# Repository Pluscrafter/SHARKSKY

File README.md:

# SHARKSKY
Ein Quadrocopter Flightcontroller für eine Maturaarbeit.

## Aufbau
Hier wird der Aufbau des Repos beschrieben.

### 01_Flightcontroller
In diesem Ordner ist der Code, und der Schaltplan des Flightcontrollers zu finden. Im Ordner Code sind die Eclipse Projekte die mit der STM32CubeIDE erstellt worden sind.

### 02_RCTransmitter
In diesem Ordner ist der Code und die Konstruktion der Fernbedienung zu finden.
### 03_Datasheets
Hier sind die nötigen Datasheets gelagert um nicht immer im Internet dannach zu suchen.

### 04_Schriftliche Arbeit
Dort ist das LaTex file für den schriftlichen Teil.

### 05_Simulatoren
Dort sind die Programme um die Filter zu testen.

### 06_Videos und Bilder
Dort sind alle Bilder zur MA.

## Benutzte Libraries
* [nRF24/RF24](https://github.com/nRF24/RF24) - Bibliothek für den Sender bzw. Empfänger
* [EminAtes/NRF24_STM32](https://github.com/EminAtes/NRF24_STM32) - Bibliothek für den Sender bzw. Empfänger übersetzt für kompitabilität mit STM32
* [jrowberg/i2cdevlib](https://github.com/jrowberg/i2cdevlib) - Bibliothek für den MPU6050
* [firebull/STM32-LCD-HD44780-I2C](https://github.com/firebull/STM32-LCD-HD44780-I2C) - Bibliothek für Hitachi LCD HD44780

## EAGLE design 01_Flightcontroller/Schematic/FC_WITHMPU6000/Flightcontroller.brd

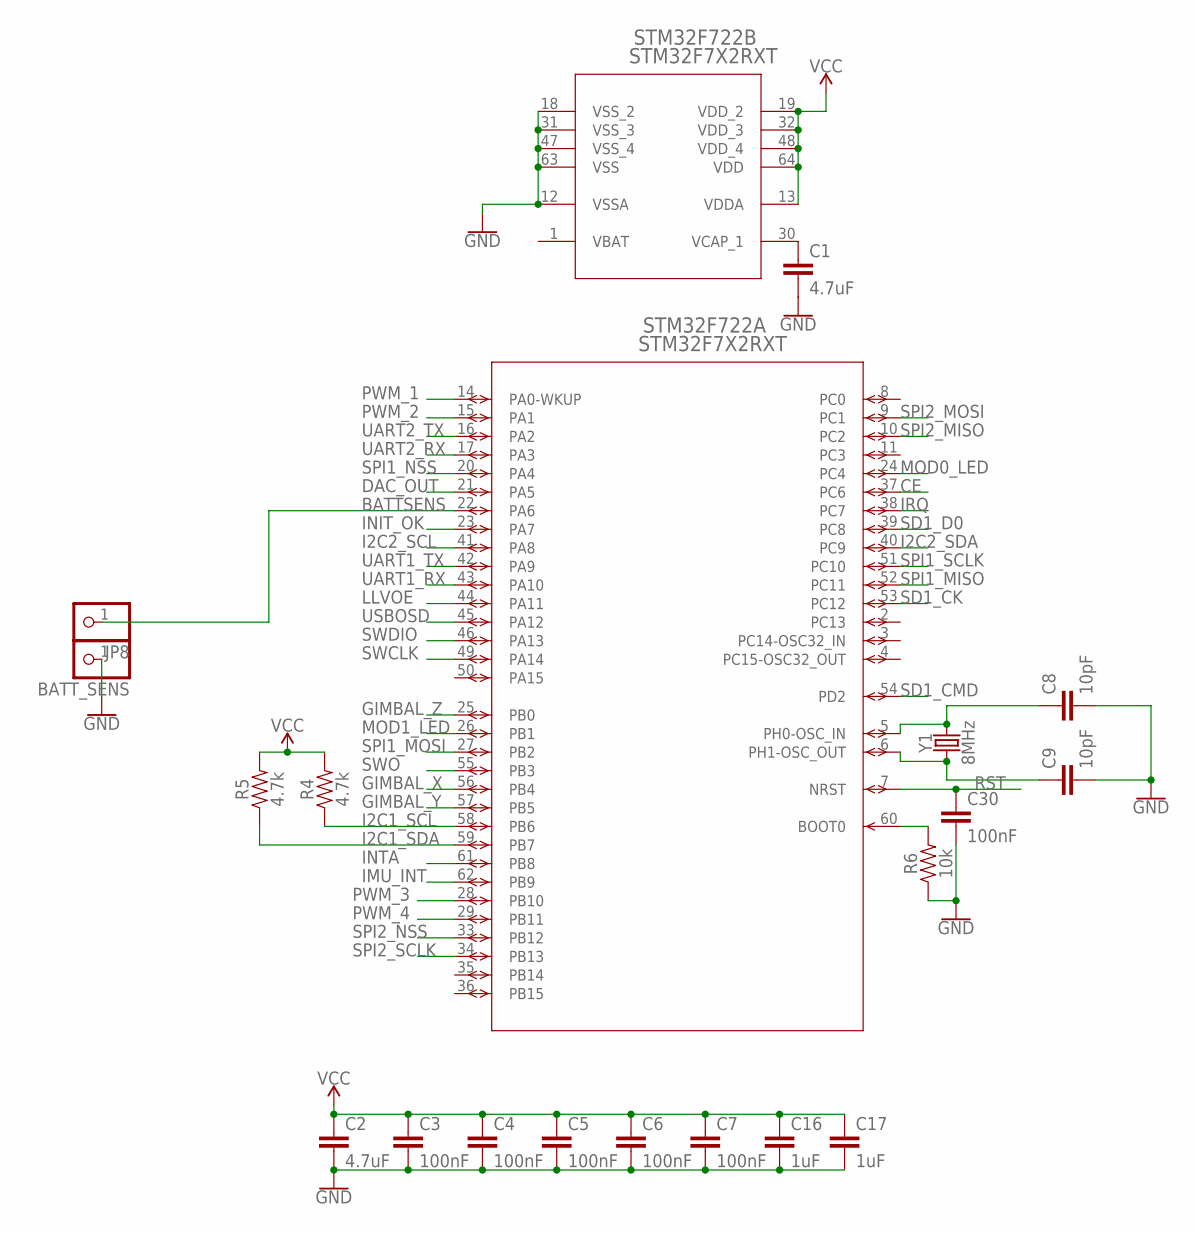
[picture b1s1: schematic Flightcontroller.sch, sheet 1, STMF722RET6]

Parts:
BATT_SENS: PINHD-1X1; 1X01
C1, C2: 4.7uF; C0805
C3, C4, C5, C6, C7, C30: 100nF; C0805
C8, C9: 10pF; C0805
C16, C17: 1uF; C0805
JP8: PINHD-1X1; 1X01
R4, R5: 4.7k; 0603
R6: 10k; 0603
STM32F722: STM32F7X2RXT; LQFP64-10X10MM
Y1: 8MHz; CRYSTAL-SMD-5X3.2-4PAD

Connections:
BATTSENS: JP8.1, STM32F722.22 (PA6)
CE: STM32F722.37 (PC6); also elsewhere on the board
DAC_OUT: STM32F722.21 (PA5); also elsewhere on the board
GIMBAL_X: STM32F722.56 (PB4); also elsewhere on the board
GIMBAL_Y: STM32F722.57 (PB5); also elsewhere on the board
GIMBAL_Z: STM32F722.25 (PB0); also elsewhere on the board
GND: BATT_SENS.1, C1.2, C2.2, C3.2, C4.2, C5.2, C6.2, C7.2, C8.2, C9.2, C16.2, C17.2, C30.2, R6.1, STM32F722.12 (VSSA), STM32F722.18 (VSS_2), STM32F722.31 (VSS_3), STM32F722.47 (VSS_4), STM32F722.63 (VSS); also elsewhere on the board
I2C1_SCL: R4.1, STM32F722.58 (PB6); also elsewhere on the board
I2C1_SDA: R5.1, STM32F722.59 (PB7); also elsewhere on the board
I2C2_SCL: STM32F722.41 (PA8); also elsewhere on the board
I2C2_SDA: STM32F722.40 (PC9); also elsewhere on the board
IMU_INT: STM32F722.62 (PB9); also elsewhere on the board
INIT_OK: STM32F722.23 (PA7); also elsewhere on the board
INTA: STM32F722.61 (PB8); also elsewhere on the board
IRQ: STM32F722.38 (PC7); also elsewhere on the board
LLVOE: STM32F722.44 (PA11); also elsewhere on the board
MOD0_LED: STM32F722.24 (PC4); also elsewhere on the board
MOD1_LED: STM32F722.26 (PB1); also elsewhere on the board
unnamed: C1.1, STM32F722.30 (VCAP_1)
unnamed: C8.1, STM32F722.5 (PH0-OSC_IN), Y1.3 (2)
unnamed: C9.1, STM32F722.6 (PH1-OSC_OUT), Y1.1
unnamed: R6.2, STM32F722.60 (BOOT0)
PWM_1: STM32F722.14 (PA0-WKUP); also elsewhere on the board
PWM_2: STM32F722.15 (PA1); also elsewhere on the board
PWM_3: STM32F722.28 (PB10); also elsewhere on the board
PWM_4: STM32F722.29 (PB11); also elsewhere on the board
RST: C30.1, STM32F722.7 (NRST); also elsewhere on the board
SD1_CK: STM32F722.53 (PC12); also elsewhere on the board
SD1_CMD: STM32F722.54 (PD2); also elsewhere on the board
SD1_D0: STM32F722.39 (PC8); also elsewhere on the board
SPI1_MISO: STM32F722.52 (PC11); also elsewhere on the board
SPI1_MOSI: STM32F722.27 (PB2); also elsewhere on the board
SPI1_NSS: STM32F722.20 (PA4); also elsewhere on the board
SPI1_SCLK: STM32F722.51 (PC10); also elsewhere on the board
SPI2_MISO: STM32F722.10 (PC2); also elsewhere on the board
SPI2_MOSI: STM32F722.9 (PC1); also elsewhere on the board
SPI2_NSS: STM32F722.33 (PB12); also elsewhere on the board
SPI2_SCLK: STM32F722.34 (PB13); also elsewhere on the board
SWCLK: STM32F722.49 (PA14); also elsewhere on the board
SWDIO: STM32F722.46 (PA13); also elsewhere on the board
SWO: STM32F722.55 (PB3); also elsewhere on the board
UART1_RX: STM32F722.43 (PA10); also elsewhere on the board
UART1_TX: STM32F722.42 (PA9); also elsewhere on the board
UART2_RX: STM32F722.17 (PA3); also elsewhere on the board
UART2_TX: STM32F722.16 (PA2); also elsewhere on the board
USBOSD: STM32F722.45 (PA12); also elsewhere on the board
VBAT: STM32F722.1 (VBAT)
VCC: C2.1, C3.1, C4.1, C5.1, C6.1, C7.1, C16.1, C17.1, R4.2, R5.2, STM32F722.13 (VDDA), STM32F722.19 (VDD_2), STM32F722.32 (VDD_3), STM32F722.48 (VDD_4), STM32F722.64 (VDD); also elsewhere on the board

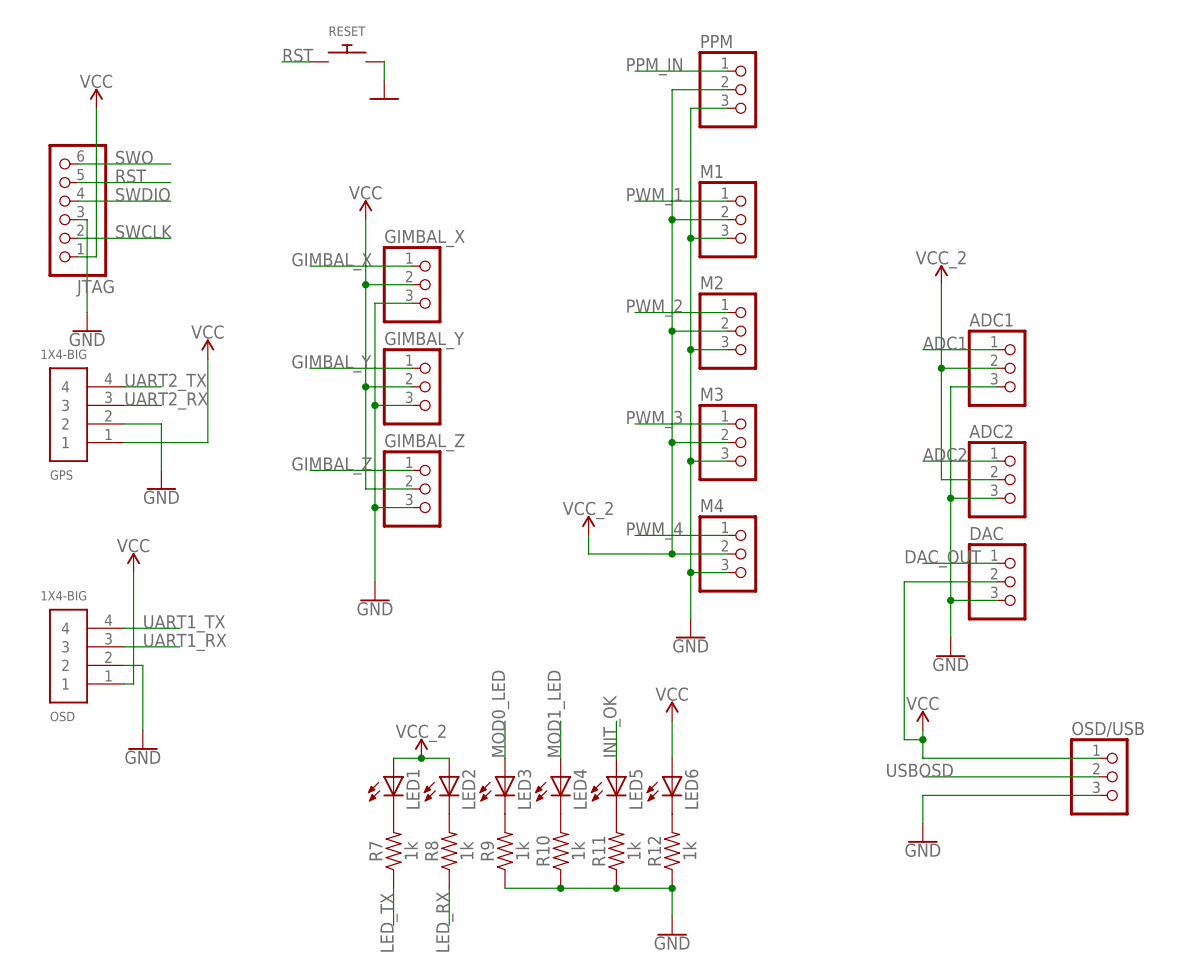
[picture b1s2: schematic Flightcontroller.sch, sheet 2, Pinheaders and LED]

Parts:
ADC1, ADC2: PINHD-1X3; 1X03
DAC: PINHD-1X3; 1X03
GIMBAL_X: PINHD-1X3; 1X03
GIMBAL_Y: PINHD-1X3; 1X03
GIMBAL_Z: PINHD-1X3; 1X03
GPS: 1X4-BIG; 1X04-BIG
JTAG: PINHD-1X6; 1X06
LED1, LED2, LED3, LED4, LED5, LED6: LEDSMT1206; 1206
M1, M2, M3, M4: PINHD-1X3; 1X03
OSD: 1X4-BIG; 1X04-BIG
OSD/USB: PINHD-1X3; 1X03
PPM: PINHD-1X3; 1X03
R7, R8, R9, R10, R11, R12: 1k; 0603
RESET: SWITCH_PUSHBUTTONC&K_KSS; BTN_CK_KSS

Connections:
ADC1: ADC1.1; also elsewhere on the board
ADC2: ADC2.1; also elsewhere on the board
DAC_OUT: DAC.1; also elsewhere on the board
GIMBAL_X: GIMBAL_X.1; also elsewhere on the board
GIMBAL_Y: GIMBAL_Y.1; also elsewhere on the board
GIMBAL_Z: GIMBAL_Z.1; also elsewhere on the board
GND: ADC1.3, ADC2.3, DAC.3, GIMBAL_X.3, GIMBAL_Y.3, GIMBAL_Z.3, GPS.2, JTAG.3, M1.3, M2.3, M3.3, M4.3, OSD.2, OSD/USB.3, PPM.3, R9.1, R10.1, R11.1, R12.1, RESET.P$2; also elsewhere on the board
INIT_OK: LED5.A; also elsewhere on the board
LED_RX: R8.1; also elsewhere on the board
LED_TX: R7.1; also elsewhere on the board
MOD0_LED: LED3.A; also elsewhere on the board
MOD1_LED: LED4.A; also elsewhere on the board
unnamed: LED1.C, R7.2
unnamed: LED2.C, R8.2
unnamed: LED3.C, R9.2
unnamed: LED4.C, R10.2
unnamed: LED5.C, R11.2
unnamed: LED6.C, R12.2
PPM_IN: PPM.1; also elsewhere on the board
PWM_1: M1.1; also elsewhere on the board
PWM_2: M2.1; also elsewhere on the board
PWM_3: M3.1; also elsewhere on the board
PWM_4: M4.1; also elsewhere on the board
RST: JTAG.5, RESET.P$1; also elsewhere on the board
SWCLK: JTAG.2; also elsewhere on the board
SWDIO: JTAG.4; also elsewhere on the board
SWO: JTAG.6; also elsewhere on the board
UART1_RX: OSD.3; also elsewhere on the board
UART1_TX: OSD.4; also elsewhere on the board
UART2_RX: GPS.3; also elsewhere on the board
UART2_TX: GPS.4; also elsewhere on the board
USBOSD: OSD/USB.2; also elsewhere on the board
VCC: DAC.2, GIMBAL_X.2, GIMBAL_Y.2, GIMBAL_Z.2, GPS.1, JTAG.1, LED6.A, OSD.1, OSD/USB.1; also elsewhere on the board
VCC_2: ADC1.2, ADC2.2, LED1.A, LED2.A, M1.2, M2.2, M3.2, M4.2, PPM.2; also elsewhere on the board

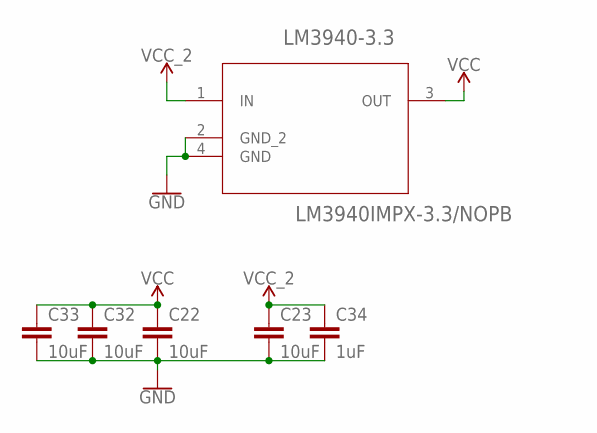
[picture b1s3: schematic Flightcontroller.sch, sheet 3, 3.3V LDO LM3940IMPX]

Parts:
C22, C23, C32, C33: 10uF; C0805
C34: 1uF; C0805
LM3940-3.3: LM3940IMPX-3.3/NOPB; SOT230P696X180-4N

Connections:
GND: C22.2, C23.2, C32.2, C33.2, C34.2, LM3940-3.3.2 (GND_2), LM3940-3.3.4 (GND); also elsewhere on the board
VCC: C22.1, C32.1, C33.1, LM3940-3.3.3 (OUT); also elsewhere on the board
VCC_2: C23.1, C34.1, LM3940-3.3.1 (IN); also elsewhere on the board

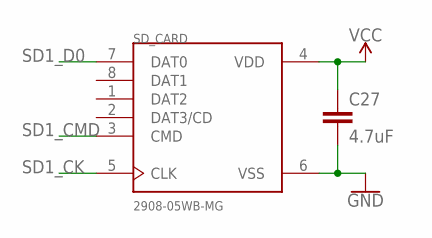
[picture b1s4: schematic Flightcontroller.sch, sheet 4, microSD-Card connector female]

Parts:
C27: 4.7uF; C0805
SD_CARD: 2908-05WB-MG; 3M_2908-05WB-MG

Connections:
GND: C27.2, SD_CARD.6 (VSS); also elsewhere on the board
SD1_CK: SD_CARD.5 (CLK); also elsewhere on the board
SD1_CMD: SD_CARD.3 (CMD); also elsewhere on the board
SD1_D0: SD_CARD.7 (DAT0); also elsewhere on the board
VCC: C27.1, SD_CARD.4 (VDD); also elsewhere on the board

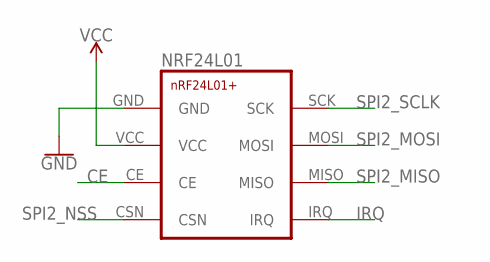
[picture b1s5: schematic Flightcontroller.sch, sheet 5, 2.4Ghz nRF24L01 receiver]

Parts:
NRF24L01: NRF24L01+

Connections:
CE: NRF24L01.CE; also elsewhere on the board
GND: NRF24L01.GND; also elsewhere on the board
IRQ: NRF24L01.IRQ; also elsewhere on the board
SPI2_MISO: NRF24L01.MISO; also elsewhere on the board
SPI2_MOSI: NRF24L01.MOSI; also elsewhere on the board
SPI2_NSS: NRF24L01.CSN; also elsewhere on the board
SPI2_SCLK: NRF24L01.SCK; also elsewhere on the board
VCC: NRF24L01.VCC; also elsewhere on the board

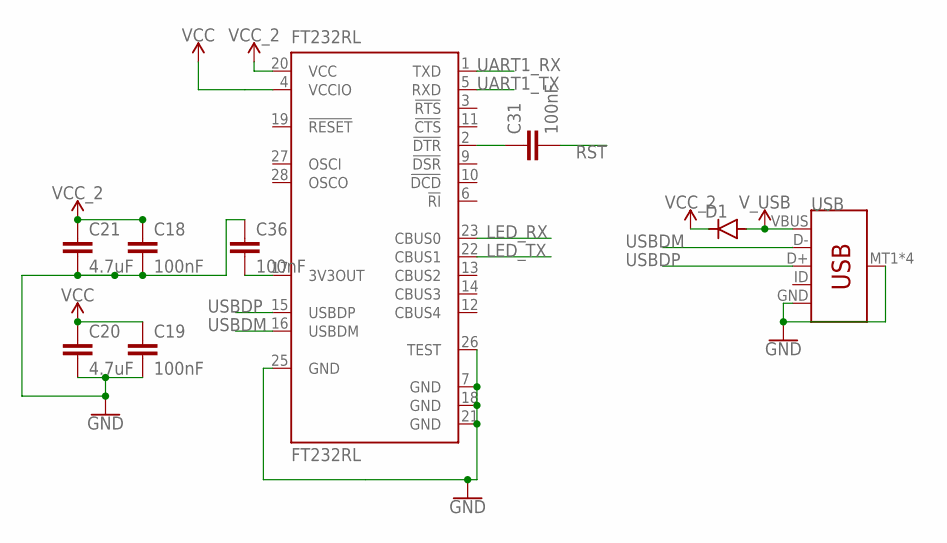
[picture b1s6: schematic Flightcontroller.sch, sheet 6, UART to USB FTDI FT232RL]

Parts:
C18, C19, C31, C36: 100nF; C0805
C20, C21: 4.7uF; C0805
D1: DIODE-DO214BA; DO214BA
FT232RL: FT232RL; SSOP28
USB: USB_MICRO-B_SMT; USB-MICROB

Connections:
GND: C18.2, C19.2, C20.2, C21.2, C36.1, FT232RL.7 (GND), FT232RL.18 (GND), FT232RL.21 (GND), FT232RL.25 (GND), FT232RL.26 (TEST), USB.GND, USB.MT1 (SHIELD), USB.MT2 (SHIELD), USB.P$1 (SHIELD), USB.P$2 (SHIELD); also elsewhere on the board
LED_RX: FT232RL.23 (CBUS0); also elsewhere on the board
LED_TX: FT232RL.22 (CBUS1); also elsewhere on the board
unnamed: C31.1, FT232RL.2 (!DTR)
unnamed: C36.2, FT232RL.17 (3V3OUT)
RST: C31.2; also elsewhere on the board
UART1_RX: FT232RL.1 (TXD); also elsewhere on the board
UART1_TX: FT232RL.5 (RXD); also elsewhere on the board
USBDM: FT232RL.16 (USBDM), USB.D-
USBDP: FT232RL.15 (USBDP), USB.D+
VCC: C19.1, C20.1, FT232RL.4 (VCCIO); also elsewhere on the board
VCC_2: C18.1, C21.1, D1.C, FT232RL.20 (VCC); also elsewhere on the board
V_USB: D1.A, USB.VBUS

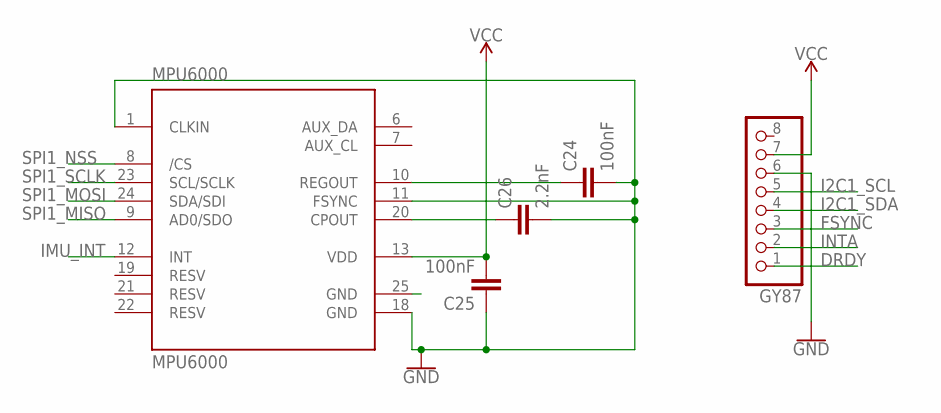
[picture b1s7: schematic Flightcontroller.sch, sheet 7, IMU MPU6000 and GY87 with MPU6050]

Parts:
C24, C25: 100nF; C0805
C26: 2.2nF; C0805
GY87: PINHD-1X8CLEANBIG; 1X08-CLEANBIG
MPU6000: MPU6000; QFN50P400X400X95-25T265X275N

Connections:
DRDY: GY87.1
FSYNC: GY87.3
GND: C24.2, C25.1, C26.2, GY87.6, MPU6000.1 (CLKIN), MPU6000.11 (FSYNC), MPU6000.18 (GND); also elsewhere on the board
I2C1_SCL: GY87.5; also elsewhere on the board
I2C1_SDA: GY87.4; also elsewhere on the board
IMU_INT: MPU6000.12 (INT); also elsewhere on the board
INTA: GY87.2; also elsewhere on the board
unnamed: C24.1, MPU6000.10 (REGOUT)
unnamed: C26.1, MPU6000.20 (CPOUT)
NC: MPU6000.25 (GND)
SPI1_MISO: MPU6000.9 (AD0/SDO); also elsewhere on the board
SPI1_MOSI: MPU6000.24 (SDA/SDI); also elsewhere on the board
SPI1_NSS: MPU6000.8 (/CS); also elsewhere on the board
SPI1_SCLK: MPU6000.23 (SCL/SCLK); also elsewhere on the board
VCC: C25.2, GY87.7, MPU6000.13 (VDD); also elsewhere on the board

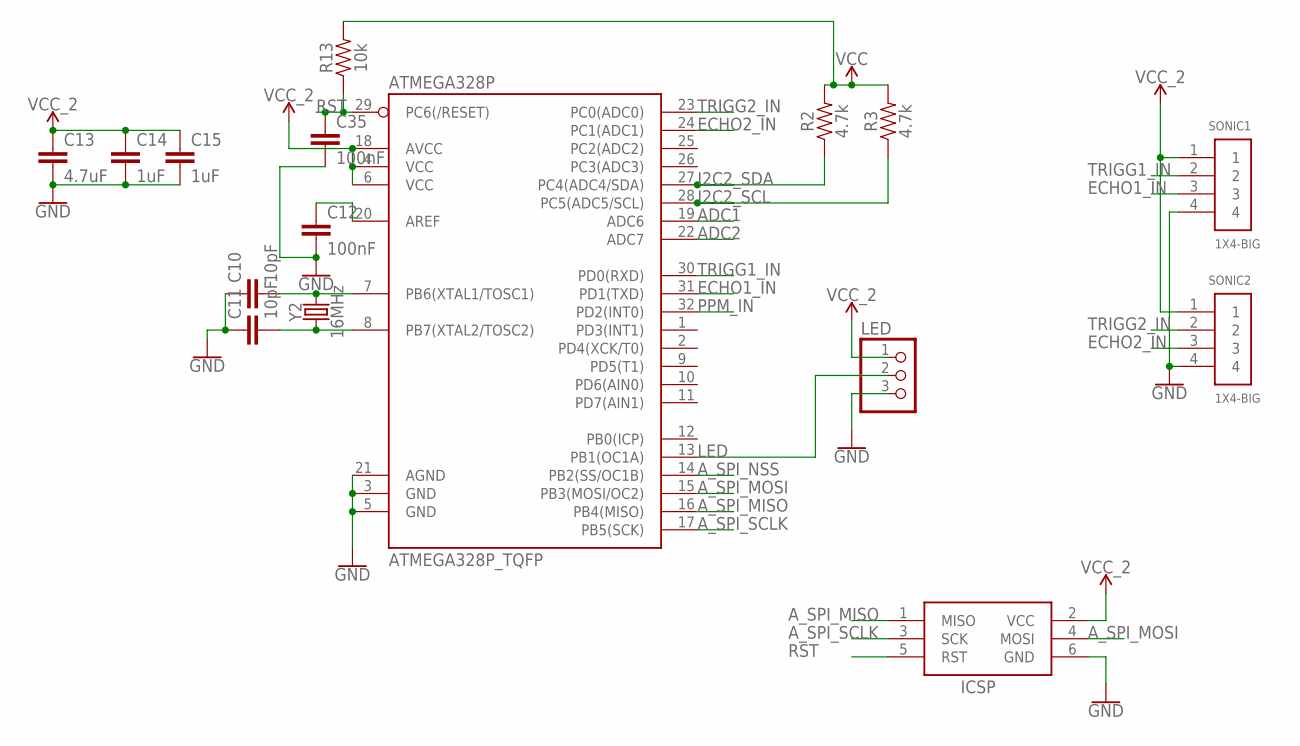
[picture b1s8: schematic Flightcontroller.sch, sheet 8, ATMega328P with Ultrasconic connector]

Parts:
ATMEGA328P: ATMEGA328P_TQFP; TQFP32-08
C10, C11: 10pF; C0805
C12, C35: 100nF; C0805
C13: 4.7uF; C0805
C14, C15: 1uF; C0805
ICSP: AVRISP-6; AVRISP
LED: PINHD-1X3; 1X03
R2, R3: 4.7k; 0603
R13: 10k; 0603
SONIC1, SONIC2: 1X4-BIG; 1X04-BIG
Y2: 16MHz; CRYSTAL-SMD-5X3.2-4PAD

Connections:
ADC1: ATMEGA328P.19 (ADC6); also elsewhere on the board
ADC2: ATMEGA328P.22 (ADC7); also elsewhere on the board
A_SPI_MISO: ATMEGA328P.16 (PB4(MISO)), ICSP.1 (MISO); also elsewhere on the board
A_SPI_MOSI: ATMEGA328P.15 (PB3(MOSI/OC2)), ICSP.4 (MOSI); also elsewhere on the board
A_SPI_NSS: ATMEGA328P.14 (PB2(SS/OC1B)); also elsewhere on the board
A_SPI_SCLK: ATMEGA328P.17 (PB5(SCK)), ICSP.3 (SCK); also elsewhere on the board
ECHO1_IN: ATMEGA328P.31 (PD1(TXD)), SONIC1.3
ECHO2_IN: ATMEGA328P.24 (PC1(ADC1)), SONIC2.3
GND: ATMEGA328P.3 (GND), ATMEGA328P.5 (GND), ATMEGA328P.21 (AGND), C10.1, C11.1, C12.2, C13.2, C14.2, C15.2, C35.2, ICSP.6 (GND), LED.3, SONIC1.4, SONIC2.4; also elsewhere on the board
I2C2_SCL: ATMEGA328P.28 (PC5(ADC5/SCL)), R3.1; also elsewhere on the board
I2C2_SDA: ATMEGA328P.27 (PC4(ADC4/SDA)), R2.1; also elsewhere on the board
LED: ATMEGA328P.13 (PB1(OC1A)), LED.2
unnamed: ATMEGA328P.20 (AREF), C12.1
unnamed: ATMEGA328P.7 (PB6(XTAL1/TOSC1)), C10.2, Y2.3 (2)
unnamed: ATMEGA328P.8 (PB7(XTAL2/TOSC2)), C11.2, Y2.1
PPM_IN: ATMEGA328P.32 (PD2(INT0)); also elsewhere on the board
RST: ATMEGA328P.29 (PC6(/RESET)), C35.1, ICSP.5 (RST), R13.1; also elsewhere on the board
TRIGG1_IN: ATMEGA328P.30 (PD0(RXD)), SONIC1.2
TRIGG2_IN: ATMEGA328P.23 (PC0(ADC0)), SONIC2.2
VCC: R2.2, R3.2, R13.2; also elsewhere on the board
VCC_2: ATMEGA328P.4 (VCC), ATMEGA328P.6 (VCC), ATMEGA328P.18 (AVCC), C13.1, C14.1, C15.1, ICSP.2 (VCC), LED.1, SONIC1.1, SONIC2.1; also elsewhere on the board

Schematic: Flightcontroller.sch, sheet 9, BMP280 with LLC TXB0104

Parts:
BMP280: BMP280
C28, C29, C37, C38: 100nF; C0805
R1: 10k; 0603
TXB0104: TXB0104; SO14

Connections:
A_SPI_MISO: TXB0104.12 (B2); also elsewhere on the board
A_SPI_MOSI: TXB0104.11 (B3); also elsewhere on the board
A_SPI_NSS: TXB0104.10 (B4); also elsewhere on the board
A_SPI_SCLK: TXB0104.13 (B1); also elsewhere on the board
B_SPI_MISO: BMP280.5 (SDO), TXB0104.3 (A2)
B_SPI_MOSI: BMP280.3 (SDI), TXB0104.4 (A3)
B_SPI_NSS: BMP280.2 (CSB), TXB0104.5 (A4)
B_SPI_SCLK: BMP280.4 (SCK), TXB0104.2 (A1)
GND: BMP280.1 (GND), BMP280.7 (GND), C28.1, C29.1, C37.1, C38.1, R1.1, TXB0104.7 (GND); also elsewhere on the board
LLVOE: R1.2, TXB0104.8 (OE); also elsewhere on the board
VCC: BMP280.6 (VDDIO), BMP280.8 (VDD), C29.2, C37.2, C38.2, TXB0104.1 (VCCA); also elsewhere on the board
VCC_2: C28.2, TXB0104.14 (VCCB); also elsewhere on the board

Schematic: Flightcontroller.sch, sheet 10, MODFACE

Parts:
JP1, JP2, JP3, JP4, JP5, JP6, JP7: PINHD-1X6; 1X06

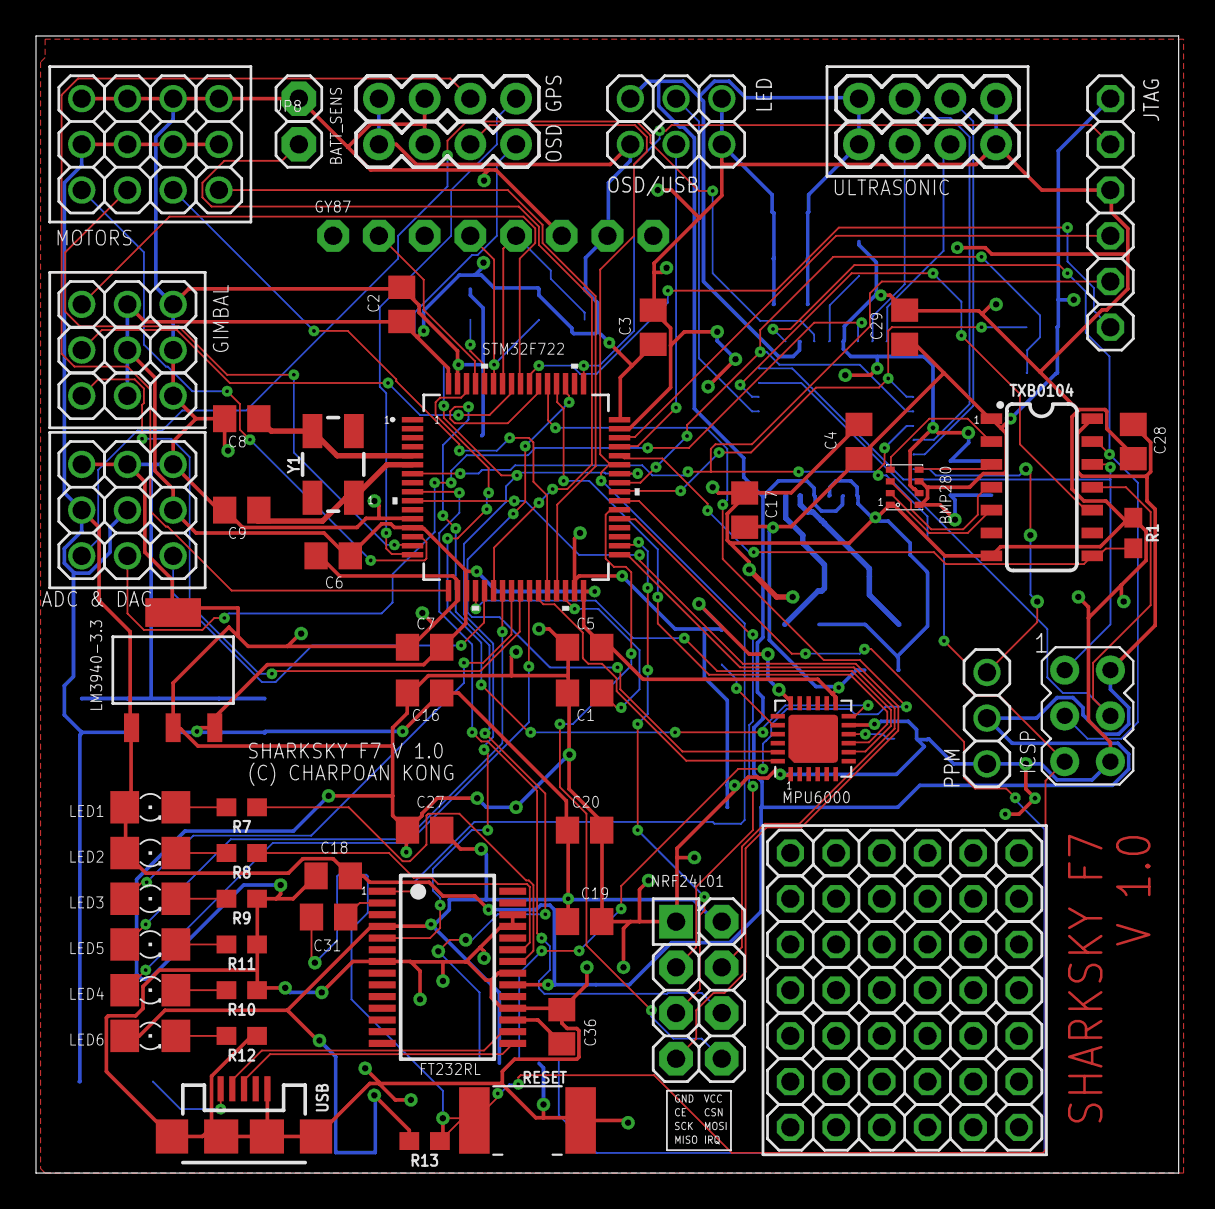
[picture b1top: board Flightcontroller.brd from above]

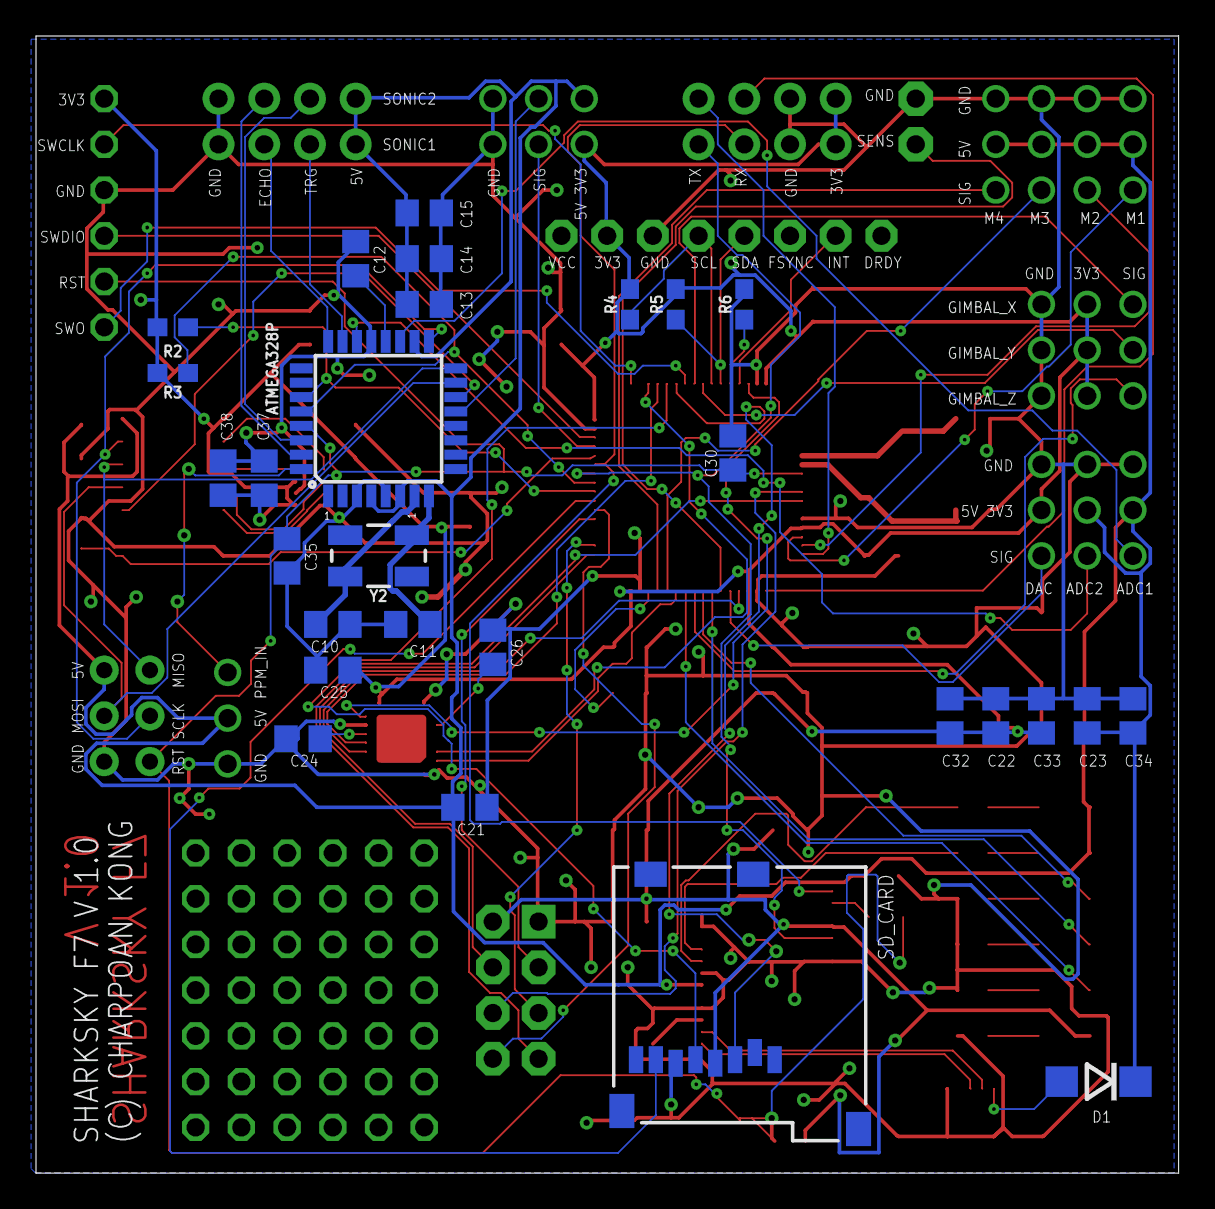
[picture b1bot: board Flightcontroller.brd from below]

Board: 2 copper layers, 63.5 x 63.2 mm, 100 parts (28 on the bottom side), 82 nets.

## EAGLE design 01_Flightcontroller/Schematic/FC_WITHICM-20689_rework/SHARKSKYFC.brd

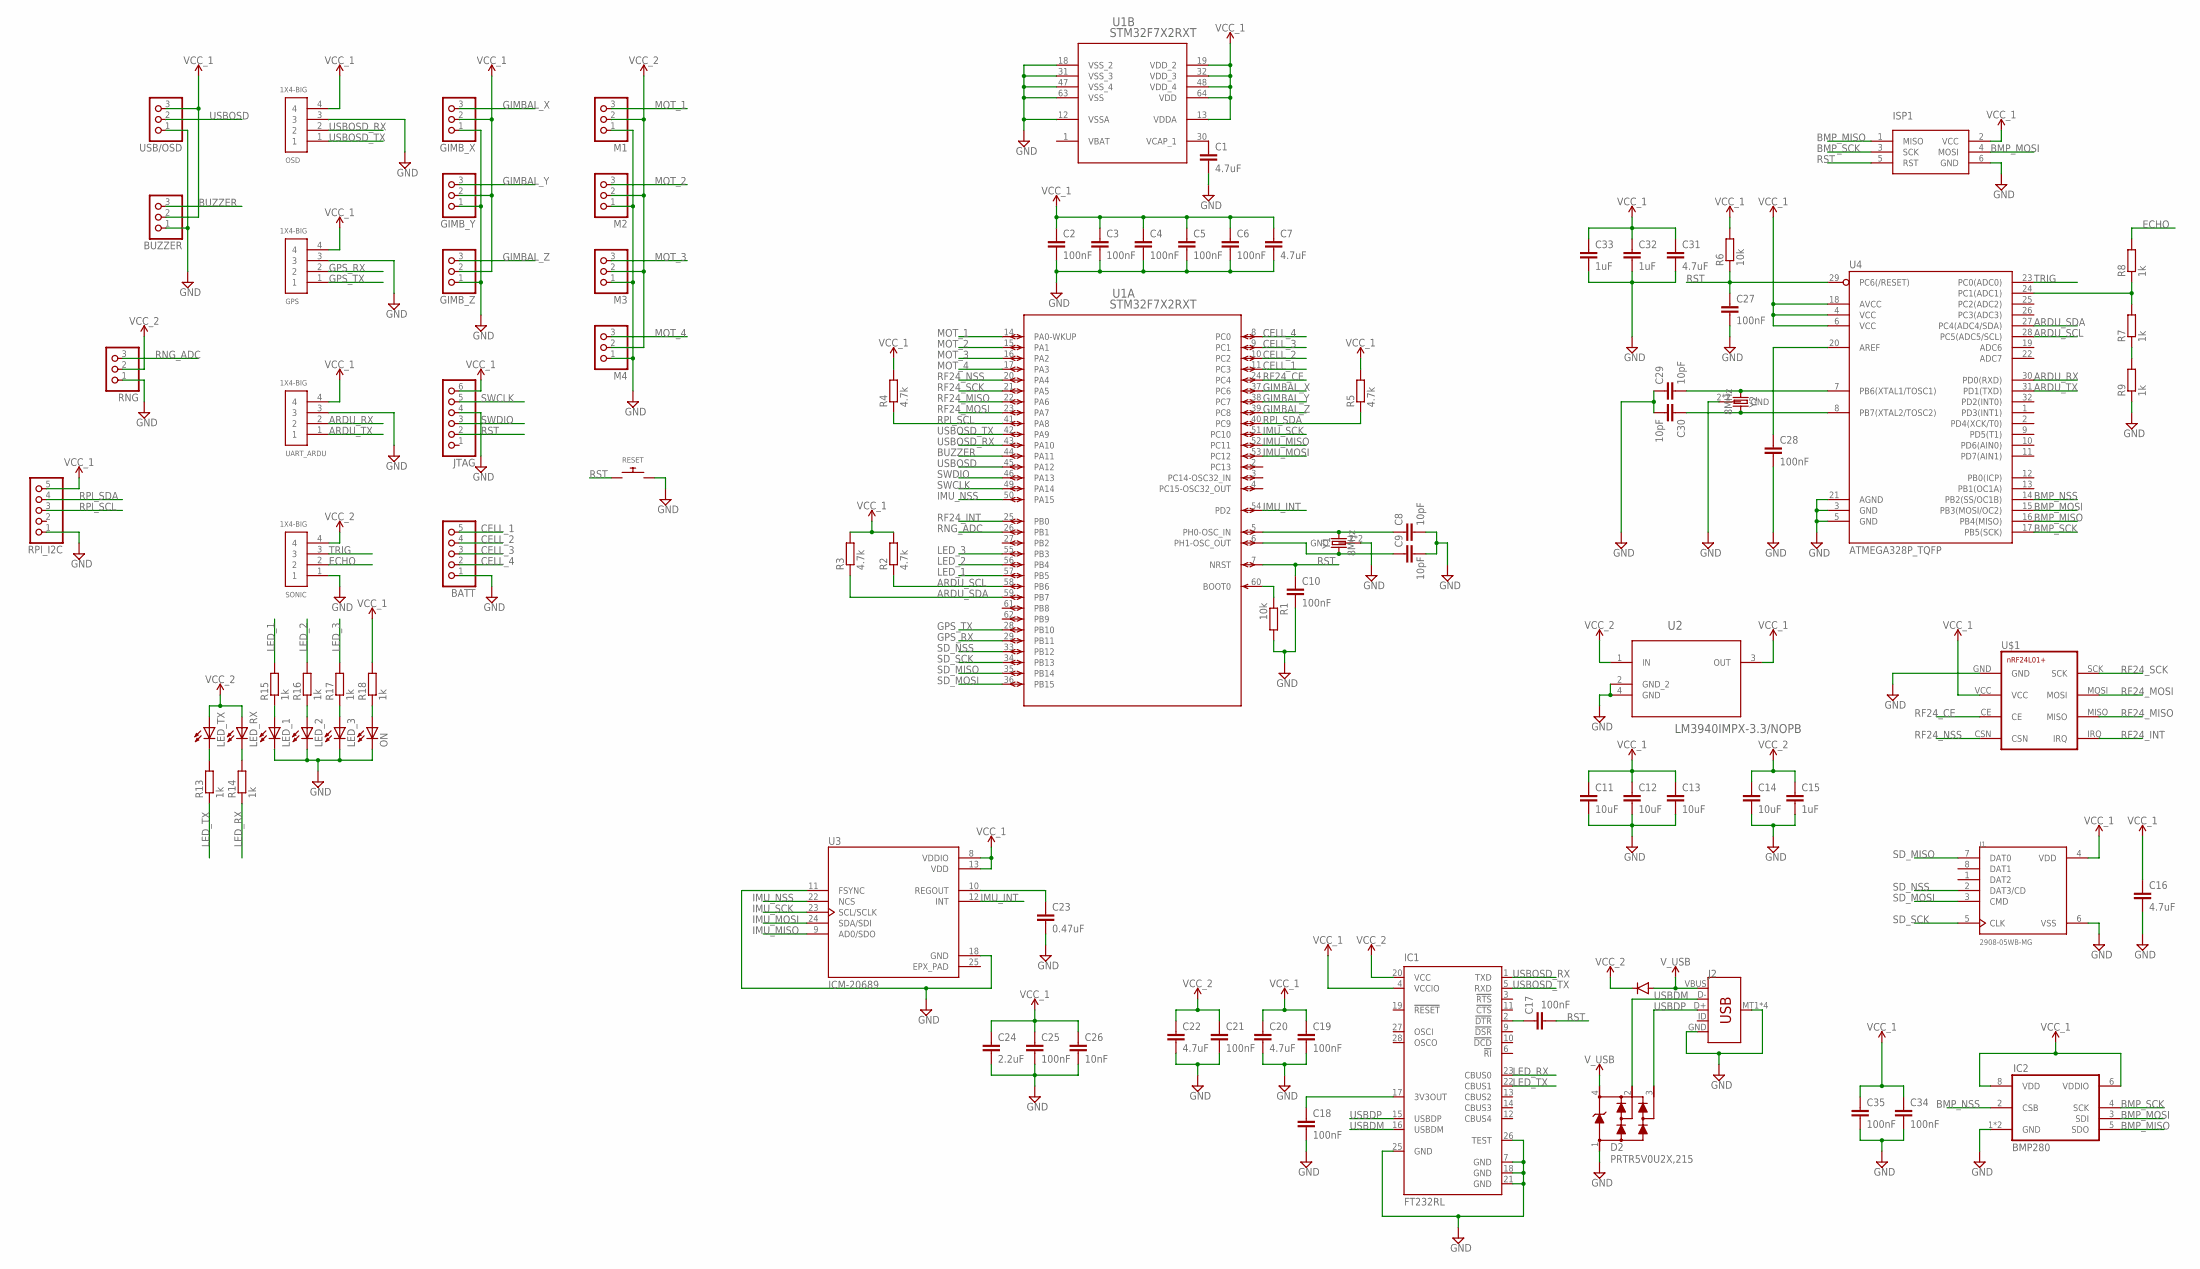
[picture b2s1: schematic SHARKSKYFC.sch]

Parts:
BATT: PINHD-1X5; 1X05
BUZZER: PINHD-1X3; 1X03
C1, C7, C16, C20, C22, C31: 4.7uF; C0805
C2, C3, C4, C5, C6, C10, C17, C18, C19, C21, C25, C27, C28, C34, C35: 100nF; C0805
C8, C9, C29, C30: 10pF; C0805
C11, C12, C13, C14: 10uF; C0805
C15, C32, C33: 1uF; C0805
C23: 0.47uF; C0805
C24: 2.2uF; C0805
C26: 10nF; C0805
D1: DIODE-DO214BA; DO214BA
D2: PRTR5V0U2X,215; SOT143B
GIMB_X: PINHD-1X3; 1X03
GIMB_Y: PINHD-1X3; 1X03
GIMB_Z: PINHD-1X3; 1X03
GPS: 1X4-BIG; 1X04-BIG
IC1: FT232RL; SSOP28
IC2: BMP280
ISP1: AVRISP-6; AVRISP
J1: 2908-05WB-MG; 3M_2908-05WB-MG
J2: USB_MICRO-B_SMT; USB-MICROB
JTAG: PINHD-1X6; 1X06
LED_1, LED_2, LED_3: LEDSMT1206; 1206
LED_RX: LEDSMT1206; 1206
LED_TX: LEDSMT1206; 1206
M1, M2, M3, M4: PINHD-1X3; 1X03
ON: LEDSMT1206; 1206
OSD: 1X4-BIG; 1X04-BIG
R1, R6: 10k; R0603
R2, R3, R4, R5: 4.7k; R0603
R7, R8, R9, R13, R14, R15, R16, R17, R18: 1k; R0603
RESET: SWITCH_PUSHBUTTONC&K_KSS; BTN_CK_KSS
RNG: PINHD-1X3; 1X03
RPI_I2C: PINHD-1X5; 1X05
SONIC: 1X4-BIG; 1X04-BIG
U1: STM32F7X2RXT; LQFP64-10X10MM
U2: LM3940IMPX-3.3/NOPB; SOT230P696X180-4N
U3: ICM-20689; QFN50P400X400X95-25N
U4: ATMEGA328P_TQFP; TQFP32-08
U$1: NRF24L01+
UART_ARDU: 1X4-BIG; 1X04-BIG
USB/OSD: PINHD-1X3; 1X03
Y1, Y2: 8MHz; CRYSTAL-SMD-5X3.2-4PAD

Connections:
ARDU_RX: U4.30 (PD0(RXD)), UART_ARDU.2
ARDU_SCL: R2.1, U1.58 (PB6), U4.28 (PC5(ADC5/SCL))
ARDU_SDA: R3.1, U1.59 (PB7), U4.27 (PC4(ADC4/SDA))
ARDU_TX: U4.31 (PD1(TXD)), UART_ARDU.1
BMP_MISO: IC2.5 (SDO), ISP1.1 (MISO), U4.16 (PB4(MISO))
BMP_MOSI: IC2.3 (SDI), ISP1.4 (MOSI), U4.15 (PB3(MOSI/OC2))
BMP_NSS: IC2.2 (CSB), U4.14 (PB2(SS/OC1B))
BMP_SCK: IC2.4 (SCK), ISP1.3 (SCK), U4.17 (PB5(SCK))
BUZZER: BUZZER.3, U1.44 (PA11)
CELL_1: BATT.5, U1.11 (PC3)
CELL_2: BATT.4, U1.10 (PC2)
CELL_3: BATT.3, U1.9 (PC1)
CELL_4: BATT.2, U1.8 (PC0)
E: R7.2, R8.1, U4.24 (PC1(ADC1))
ECHO: R8.2, SONIC.2
EPX_PAD: U3.25 (EPX_PAD)
GIMBAL_X: GIMB_X.3, U1.37 (PC6)
GIMBAL_Y: GIMB_Y.3, U1.38 (PC7)
GIMBAL_Z: GIMB_Z.3, U1.39 (PC8)
GND: BATT.1, BUZZER.1, C1.2, C2.2, C3.2, C4.2, C5.2, C6.2, C7.2, C8.2, C9.2, C10.2, C11.2, C12.2, C13.2, C14.2, C15.2, C16.2, C18.2, C19.2, C20.2, C21.2, C22.2, C23.2, C24.2, C25.2, C26.2, C27.2, C28.2, C29.1, C30.2, C31.2, C32.2, C33.2, C34.2, C35.2, D2.1, GIMB_X.1, GIMB_Y.1, GIMB_Z.1, GPS.3, IC1.7 (GND), IC1.18 (GND), IC1.21 (GND), IC1.25 (GND), IC1.26 (TEST), IC2.1 (GND), IC2.7 (GND), ISP1.6 (GND), J1.6 (VSS), J2.GND, J2.MT1 (SHIELD), J2.MT2 (SHIELD), J2.P$1 (SHIELD), J2.P$2 (SHIELD), JTAG.4, LED_1.C, LED_2.C, LED_3.C, M1.1, M2.1, M3.1, M4.1, ON.C, OSD.3, R1.2, R9.1, RESET.P$2, RNG.1, RPI_I2C.1, SONIC.1, U1.12 (VSSA), U1.18 (VSS_2), U1.31 (VSS_3), U1.47 (VSS_4), U1.63 (VSS), U2.2 (GND_2), U2.4 (GND), U3.11 (FSYNC), U3.18 (GND), U4.3 (GND), U4.5 (GND), U4.21 (AGND), U$1.GND, UART_ARDU.3, USB/OSD.1, Y1.2 (GND), Y1.4 (GND), Y2.2 (GND), Y2.4 (GND)
GPS_RX: GPS.2, U1.29 (PB11)
GPS_TX: GPS.1, U1.28 (PB10)
IMU_INT: U1.54 (PD2), U3.12 (INT)
IMU_MISO: U1.52 (PC11), U3.9 (AD0/SDO)
IMU_MOSI: U1.53 (PC12), U3.24 (SDA/SDI)
IMU_NSS: U1.50 (PA15), U3.22 (NCS)
IMU_SCK: U1.51 (PC10), U3.23 (SCL/SCLK)
LED_1: R15.2, U1.57 (PB5)
LED_2: R16.2, U1.56 (PB4)
LED_3: R17.2, U1.55 (PB3)
LED_RX: IC1.23 (CBUS0), R14.1
LED_TX: IC1.22 (CBUS1), R13.1
MOT_1: M1.3, U1.14 (PA0-WKUP)
MOT_2: M2.3, U1.15 (PA1)
MOT_3: M3.3, U1.16 (PA2)
MOT_4: M4.3, U1.17 (PA3)
unnamed: C1.1, U1.30 (VCAP_1)
unnamed: C17.1, IC1.2 (!DTR)
unnamed: C9.1, U1.6 (PH1-OSC_OUT), Y1.1
unnamed: R1.1, U1.60 (BOOT0)
unnamed: C18.1, IC1.17 (3V3OUT)
unnamed: C23.1, U3.10 (REGOUT)
unnamed: C28.1, U4.20 (AREF)
unnamed: C29.2, U4.7 (PB6(XTAL1/TOSC1)), Y2.1
unnamed: C30.1, U4.8 (PB7(XTAL2/TOSC2)), Y2.3 (2)
unnamed: R7.1, R9.2
unnamed: LED_TX.C, R13.2
unnamed: LED_RX.C, R14.2
unnamed: LED_1.A, R15.1
unnamed: LED_2.A, R16.1
unnamed: LED_3.A, R17.1
unnamed: ON.A, R18.1
unnamed: C8.1, U1.5 (PH0-OSC_IN), Y1.3 (2)
RF24_CE: U1.24 (PC4), U$1.CE
RF24_INT: U1.25 (PB0), U$1.IRQ
RF24_MISO: U1.22 (PA6), U$1.MISO
RF24_MOSI: U1.23 (PA7), U$1.MOSI
RF24_NSS: U1.20 (PA4), U$1.CSN
RF24_SCK: U1.21 (PA5), U$1.SCK
RNG_ADC: RNG.3, U1.26 (PB1)
RPI_SCL: R4.1, RPI_I2C.3, U1.41 (PA8)
RPI_SDA: R5.1, RPI_I2C.4, U1.40 (PC9)
RST: C10.1, C17.2, C27.1, ISP1.5 (RST), JTAG.2, R6.1, RESET.P$1, U1.7 (NRST), U4.29 (PC6(/RESET))
SD_MISO: J1.7 (DAT0), U1.35 (PB14)
SD_MOSI: J1.3 (CMD), U1.36 (PB15)
SD_NSS: J1.2 (DAT3/CD), U1.33 (PB12)
SD_SCK: J1.5 (CLK), U1.34 (PB13)
SWCLK: JTAG.5, U1.49 (PA14)
SWDIO: JTAG.3, U1.46 (PA13)
TRIG: SONIC.3, U4.23 (PC0(ADC0))
USBDM: D2.2, IC1.16 (USBDM), J2.D-
USBDP: D2.3, IC1.15 (USBDP), J2.D+
USBOSD: U1.45 (PA12), USB/OSD.2
USBOSD_RX: IC1.1 (TXD), OSD.2, U1.43 (PA10)
USBOSD_TX: IC1.5 (RXD), OSD.1, U1.42 (PA9)
VBAT: U1.1 (VBAT)
VCC_1: BUZZER.2, C2.1, C3.1, C4.1, C5.1, C6.1, C7.1, C11.1, C12.1, C13.1, C16.1, C19.1, C20.1, C24.1, C25.1, C26.1, C31.1, C32.1, C33.1, C34.1, C35.1, GIMB_X.2, GIMB_Y.2, GIMB_Z.2, GPS.4, IC1.4 (VCCIO), IC2.6 (VDDIO), IC2.8 (VDD), ISP1.2 (VCC), J1.4 (VDD), JTAG.6, OSD.4, R2.2, R3.2, R4.2, R5.2, R6.2, R18.2, RPI_I2C.5, U1.13 (VDDA), U1.19 (VDD_2), U1.32 (VDD_3), U1.48 (VDD_4), U1.64 (VDD), U2.3 (OUT), U3.8 (VDDIO), U3.13 (VDD), U4.4 (VCC), U4.6 (VCC), U4.18 (AVCC), U$1.VCC, UART_ARDU.4, USB/OSD.3
VCC_2: C14.1, C15.1, C21.1, C22.1, D1.C, IC1.20 (VCC), LED_RX.A, LED_TX.A, M1.2, M2.2, M3.2, M4.2, RNG.2, SONIC.4, U2.1 (IN)
V_USB: D1.A, D2.4, J2.VBUS

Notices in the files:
parts and their libraries:
SparkFun-PowerSymbols: Licensing: Creative Commons ShareAlike 4.0 International - https://creativecommons.org/licenses/by-sa/4.0
